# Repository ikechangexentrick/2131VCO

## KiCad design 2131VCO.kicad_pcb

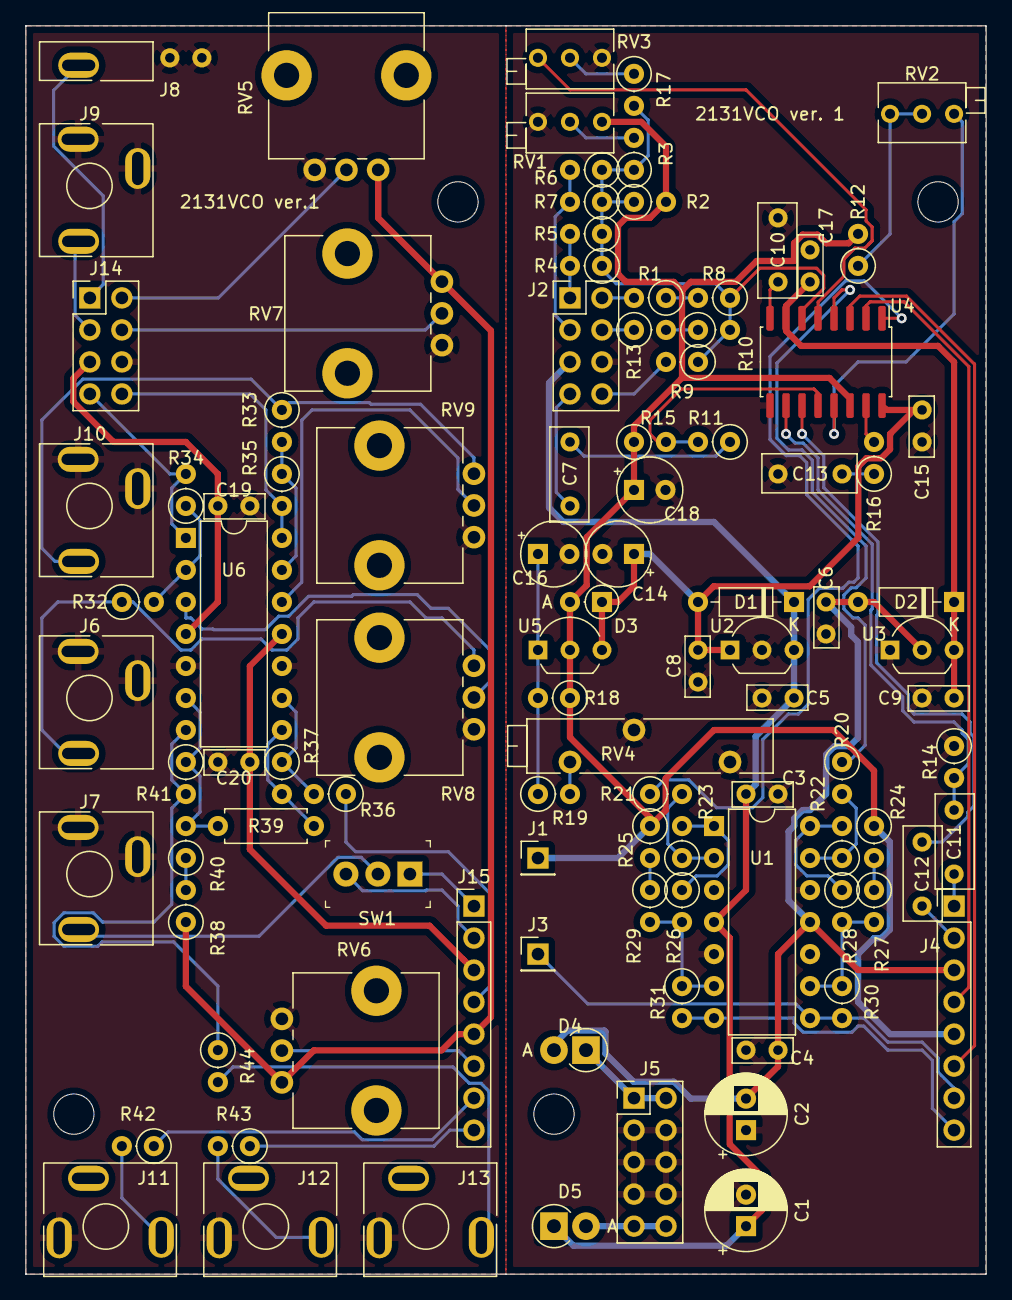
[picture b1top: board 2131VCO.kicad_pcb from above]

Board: 2 copper layers, 76.2 x 99.1 mm, 100 parts (0 on the bottom side), 75 nets.

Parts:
C1, C2: 100u; CP_Radial_D6.3mm_P2.50mm
C3, C4, C5, C6, C8, C9, C15, C17, C19, C20: 0.1u; C_Axial_L4.8mm_D2.0mm_P2.54mm_Horizontal
C7: 1u; C_Axial_L4.8mm_D3.1mm_P5.08mm_Horizontal
C10: 3900p; C_Axial_L4.8mm_D3.1mm_P5.08mm_Horizontal
C11, C12, C13: 0.01u; C_Axial_L4.8mm_D3.1mm_P5.08mm_Horizontal
C14, C18: 1u; CP_Radial_Tantal_D5.0mm_P2.50mm
C16: 10u; CP_Radial_Tantal_D5.0mm_P2.50mm
D1, D2: 1N4148; D_DO-35_SOD27_P7.62mm_Horizontal
D3: 1N4148; D_DO-35_SOD27_P2.54mm_Vertical_AnodeUp
D4, D5: D_Schottky; D_DO-41_SOD81_P2.54mm_Vertical_AnodeUp
J1: Vref; PinHeader_1x01_P2.54mm_Vertical
J2, J14: bus_L; PinHeader_2x04_P2.54mm_Vertical
J3: tri; PinHeader_1x01_P2.54mm_Vertical
J4, J15: bus_R; PinHeader_1x08_P2.54mm_Vertical
J5: power_bus; PinHeader_2x05_P2.54mm_Vertical
J6: lin FM; MJ-355_3.5mm_mono_jack
J7: sync; MJ-355_3.5mm_mono_jack
J8: V/oct_1; MJ-355_3.5mm_mono_jack_terminal_only
J9: V/oct_2; MJ-355_3.5mm_mono_jack
J10: exp FM; MJ-355_3.5mm_mono_jack
J11: tri_out; MJ-355_3.5mm_mono_jack
J12: saw_out; MJ-355_3.5mm_mono_jack
J13: squ_out; MJ-355_3.5mm_mono_jack
R1, R42, R43, R44: 1k; R_Axial_DIN0207_L6.3mm_D2.5mm_P2.54mm_Vertical
R2: 51k; R_Axial_DIN0207_L6.3mm_D2.5mm_P2.54mm_Vertical
R3, R4, R5, R6, R7, R32, R33, R34, R35: 100k; R_Axial_DIN0207_L6.3mm_D2.5mm_P2.54mm_Vertical
R8, R14, R20, R21, R22, R23, R36, R37: 10k; R_Axial_DIN0207_L6.3mm_D2.5mm_P2.54mm_Vertical
R9: 200k; R_Axial_DIN0207_L6.3mm_D2.5mm_P2.54mm_Vertical
R10: 120k; R_Axial_DIN0207_L6.3mm_D2.5mm_P2.54mm_Vertical
R11, R15: 510k; R_Axial_DIN0207_L6.3mm_D2.5mm_P2.54mm_Vertical
R12: 22k; R_Axial_DIN0207_L6.3mm_D2.5mm_P2.54mm_Vertical
R13: 5k; R_Axial_DIN0207_L6.3mm_D2.5mm_P2.54mm_Vertical
R16: 270; R_Axial_DIN0207_L6.3mm_D2.5mm_P2.54mm_Vertical
R17: 270k; R_Axial_DIN0207_L6.3mm_D2.5mm_P2.54mm_Vertical
R18: 240; R_Axial_DIN0207_L6.3mm_D2.5mm_P2.54mm_Vertical
R19: 150; R_Axial_DIN0207_L6.3mm_D2.5mm_P2.54mm_Vertical
R24, R25, R26, R27, R28, R29, R38, R40: 3k; R_Axial_DIN0207_L6.3mm_D2.5mm_P2.54mm_Vertical
R30, R31, R41: 12k; R_Axial_DIN0207_L6.3mm_D2.5mm_P2.54mm_Vertical
R39: 3k; R_Axial_DIN0207_L6.3mm_D2.5mm_P7.62mm_Horizontal
RV1: 10k; Potentiometer_Bourns_3266Z_Horizontal
RV2, RV3: 5k; Potentiometer_Bourns_3266Z_Horizontal
RV4: 200; Potentiometer_Bourns_3005_Horizontal
RV5, RV6, RV7, RV8, RV9: 10k; Potentiometer_Alps_RK09L_Single_Vertical
SW1: sync; Switch_Toggle_on-off-on_akizuki
U1, U6: TL074; DIP-14_W7.62mm
U2: L78L05_TO92; TO-92_Inline_Wide
U3: L79L05_TO92; TO-92_Inline_Wide
U4: SSI2131; SO-16_5.3x10.2mm_P1.27mm
U5: LM317L_TO92; TO-92_Inline_Wide

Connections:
+5V: C8.2, C14.1, C15.2, D1.2, D3.1, U2.1, U4.16, U5.3
+12V: C1.1, C3.2, C5.2, C19.2, D1.1, D5.1, J2.5, J14.5, U1.4, U2.3, U6.4
-5V: C9.1, C17.2, D2.1, U3.3, U4.7
-12V: C2.2, C4.1, C6.1, C20.1, D2.2, D4.2, J4.3, J15.3, U1.11, U3.2, U6.11
/module_core/PWM: J4.6, U4.3
/module_core/Vref: C18.1, D3.2, J1.1, J4.5, R2.2, R12.2, R15.1, R18.1, R24.1, R25.1, RV1.1, U4.14, U5.2
/module_core/exp_fm: J2.8, R9.2
/module_core/fine: J2.4, R13.1
/module_core/freq: J2.2, R1.2
/module_core/h_sync: C11.2, J4.1
/module_core/lin_fm: C7.1, J2.7
/module_core/s_sync: C12.2, J4.2
/module_core/saw_out: J4.8, R31.2, U1.7
/module_core/squ: J4.4, U4.2
/module_core/tri_out: J3.1, J4.7, R30.2, U1.8
/module_core/voct1: J2.1, R4.2, R5.2
/module_core/voct2: J2.3, R6.2, R7.2
/module_interface/PWM: J15.6, RV6.2
/module_interface/Vref: J15.5, R38.1, RV5.3, RV6.3, RV7.3
/module_interface/exp_fm: J14.8, R35.2, U6.14
/module_interface/fine: J14.4, RV7.2
/module_interface/freq: J14.2, RV5.2
/module_interface/h_sync: J15.1, SW1.1
/module_interface/lin_fm: J14.7, R34.2, U6.1
/module_interface/s_sync: J15.2, SW1.3
/module_interface/saw_out: J15.8, R43.1
/module_interface/squ: J15.4, R36.1
/module_interface/tri_out: J15.7, R42.1
/module_interface/voct1: J8.T, J14.1
/module_interface/voct2: J9.T, J14.3
GND: C1.2, C2.1, C3.1, C4.2, C5.1, C6.2, C8.1, C9.2, C10.2, C13.1, C14.2, C15.1, C16.2, C17.1, C18.2, C19.1, C20.2, J2.6, J5.3, J5.4, J5.5, J5.6, J5.7, J5.8, J6.S, J6.TN, J7.S, J7.TN, J8.S, J8.TN, J9.S, J9.TN, J10.S, J10.TN, J11.S, J12.S, J13.S, J14.6, R14.1, RV1.3, RV3.1, RV4.1, RV4.2, RV5.1, RV6.1, RV7.1, RV8.1, RV9.1, U1.3, U1.5, U1.10, U1.12, U2.2, U3.1, U4.9, U6.5, U6.10
unnamed: C7.2, R11.1
unnamed: C10.1, U4.8
unnamed: C11.1, R14.2, U4.10
unnamed: C12.1, U4.11
unnamed: C13.2, R16.1
unnamed: C16.1, R18.2, R19.1, U5.1
unnamed: D4.1, J5.1, J5.2
unnamed: D5.2, J5.9, J5.10
unnamed: J6.T, R32.1, RV8.3
unnamed: J7.T, SW1.2
unnamed: J10.T, R33.1, RV9.3
unnamed: J11.T, R42.2
unnamed: J12.T, R43.2
unnamed: J13.T, R44.2
unnamed: R1.1, R8.2
unnamed: R3.2, RV1.2
unnamed: R10.1, R13.2
unnamed: R2.1, R3.1, R4.1, R5.1, R6.1, R7.1, R8.1, R9.1, R10.2, R17.2, U4.6
unnamed: R11.2, R15.2, U4.12
unnamed: R12.1, RV2.1, RV2.2
unnamed: R16.2, U4.15
unnamed: R17.1, RV3.2
unnamed: R19.2, RV4.3
unnamed: R20.1, U4.4
unnamed: R20.2, R22.1, U1.13
unnamed: R21.1, U4.1
unnamed: R21.2, R23.1, U1.2
unnamed: R22.2, R28.1, U1.14
unnamed: R23.2, R26.1, U1.1
unnamed: R24.2, R27.1
unnamed: R25.2, R29.1
unnamed: R26.2, R29.2, R31.1, U1.6
unnamed: R27.2, R28.2, R30.1, U1.9
unnamed: R32.2, R34.1, U6.2
unnamed: R33.2, R35.1, U6.13
unnamed: R36.2, R37.1, U6.9
unnamed: R37.2, R39.1, U6.8
unnamed: R38.2, R40.1
unnamed: R39.2, R40.2, R41.1, U6.6
unnamed: R41.2, R44.1, U6.7
unnamed: RV2.3, U4.13
unnamed: RV3.3, U4.5
unnamed: RV8.2, U6.3
unnamed: RV9.2, U6.12

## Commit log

2023-04-07 2131VCO. first version of schematic.
2023-04-07 Artworks on pcbs are done.
2023-04-07 Fixed a minor problem; - position of HF_track and init_freq trimmers - marking in the front panel
